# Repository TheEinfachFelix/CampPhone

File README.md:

# CampPhone

https://wolles-elektronikkiste.de/sim800l-modul

Gruppen Anruf
https://stackoverflow.com/questions/60790790/how-can-i-start-a-conference-call-on-gsm-network

Datasheet
https://www.makershop.de/download/Datasheet_SIM800L.pdf

Infos zu sim800L
https://dasraspberrypi.de/sim800l-gsm-gps-raspberry-4/

Sim 1:  4915756785137

Warum habe ich mich dagegen entschieden, das Sim Modul selber zu implementieren? Ich habe kein Chip gefunden, der günstiger als das fertige Modul war, und ein Datenblatt in Englischer Sprache hat.

GPS Module:
https://www.lcsc.com/product-detail/GNSS-Modules_ZHONGKEWEI-ATGM336H-5N31_C90770.html

Doku Dazu
https://medium.com/@joshhrisko/portable-gps-tracker-with-arduino-3affead7ba12
Ne lib dazu
https://github.com/mikalhart/TinyGPSPlus

Zum Display
https://buyepaper.com/products/27-inch-e-ink-touch-screen-spi-interface-4-grayscale-gdey027t91-t01
https://de.aliexpress.com/item/1005004887416350.html?src=google&pdp_npi=4@dis!EUR!13.39!13.39!!!!!@!12000030898082751!ppc!!!

Daten
https://www.good-display.com/product/259.html

FT6336U Touch Chip

Hier ne lib fürs display
https://github.com/ZinggJM/GxEPD2

Und fürs Touch
https://github.com/aselectroworks/Arduino-FT6336U

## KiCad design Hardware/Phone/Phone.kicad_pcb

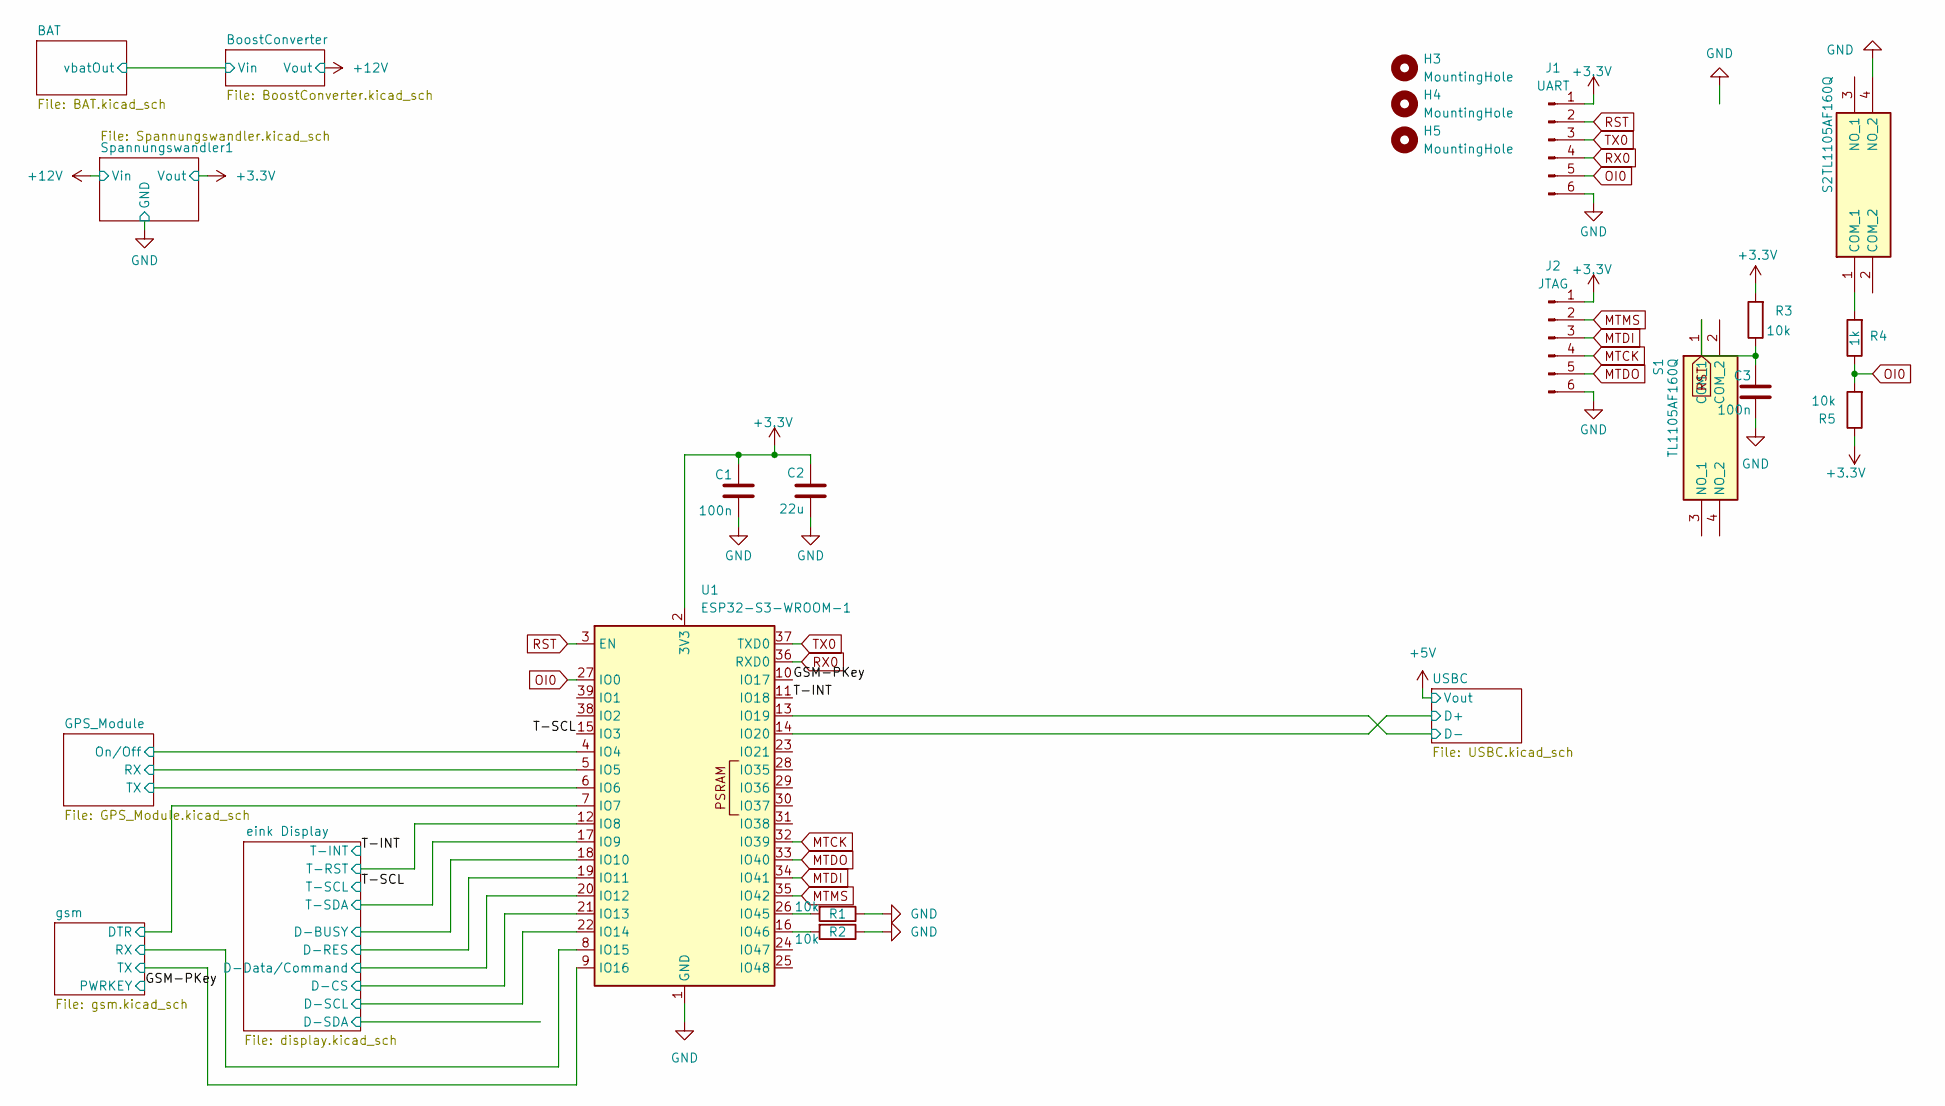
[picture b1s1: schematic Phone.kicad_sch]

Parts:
C1, C3: 100n; C_0603_1608Metric
C2: 22u; C_0603_1608Metric
H3, H4, H5: MountingHole; MountingHole_3.2mm_M3
J1: UART; 490107670612
J2: JTAG; 490107670612
R1, R2, R3, R5: 10k; R_0603_1608Metric
R4: 1k; R_0603_1608Metric
S1, S2: TL1105AF160Q; Mouser Part Number 612-TL1105A
U1: ESP32-S3-WROOM-1; ESP32-S3-WROOM-1U

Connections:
+3.3V: C1.2, C2.2, J1.1, J2.1, R3.2, R5.1, U1.2 (3V3); also elsewhere on the board
/GPS_Module/On/Off: U1.4 (IO4); also elsewhere on the board
/GPS_Module/RX: U1.5 (IO5); also elsewhere on the board
/GPS_Module/TX: U1.6 (IO6); also elsewhere on the board
/GSM-PKey: U1.10 (IO17); also elsewhere on the board
/T-INT: U1.11 (IO18); also elsewhere on the board
/T-SCL: U1.15 (IO3); also elsewhere on the board
/USBC/D+: U1.14 (IO20); also elsewhere on the board
/USBC/D-: U1.13 (IO19); also elsewhere on the board
/eink Display/D-BUSY: U1.18 (IO10); also elsewhere on the board
/eink Display/D-CS: U1.21 (IO13); also elsewhere on the board
/eink Display/D-Data/Command: U1.20 (IO12); also elsewhere on the board
/eink Display/D-RES: U1.19 (IO11); also elsewhere on the board
/eink Display/D-SCL: U1.22 (IO14); also elsewhere on the board
/eink Display/T-RST: U1.12 (IO8); also elsewhere on the board
/eink Display/T-SDA: U1.17 (IO9); also elsewhere on the board
/gsm/DTR: U1.7 (IO7); also elsewhere on the board
/gsm/RX: U1.8 (IO15); also elsewhere on the board
/gsm/TX: U1.9 (IO16); also elsewhere on the board
GND: C1.1, C2.1, C3.1, J1.6, J2.6, R1.1, R2.1, S2.4 (NO_2), U1.1 (GND), U1.40 (GND), U1.41 (GND); also elsewhere on the board
MTCK: J2.4, U1.32 (IO39)
MTDI: J2.3, U1.34 (IO41)
MTDO: J2.5, U1.33 (IO40)
MTMS: J2.2, U1.35 (IO42)
unnamed: R4.2, S2.1 (COM_1)
unnamed: R1.2, U1.26 (IO45)
unnamed: R2.2, U1.16 (IO46)
OI0: J1.5, R4.1, R5.2, U1.27 (IO0)
RST: C3.2, J1.2, R3.1, S1.1 (COM_1), U1.3 (EN)
RX0: J1.4, U1.36 (RXD0)
TX0: J1.3, U1.37 (TXD0)

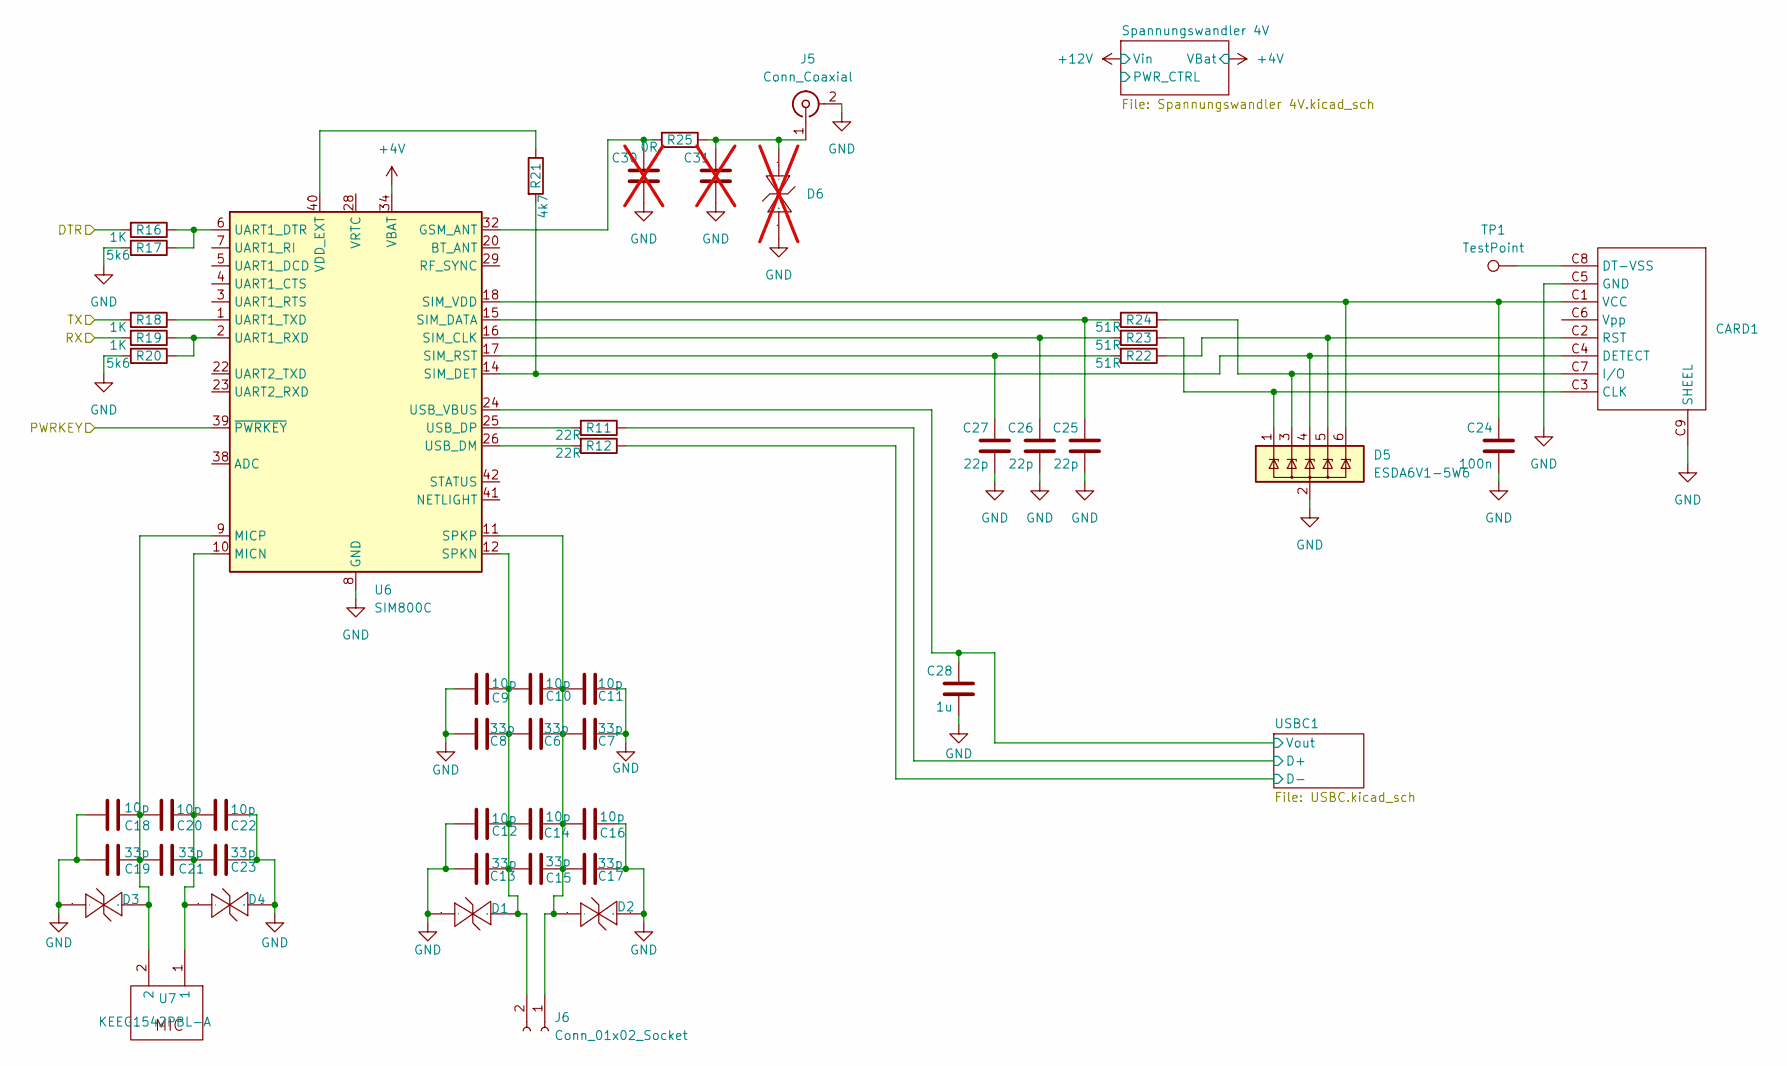
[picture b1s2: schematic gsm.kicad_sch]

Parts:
C6, C7, C8, C13, C15, C17, C19, C21, C23: 33p; C_0603_1608Metric
C9, C10, C11, C12, C14, C16, C18, C20, C22: 10p; C_0603_1608Metric
C24: 100n; C_0603_1608Metric
C25, C26, C27: 22p; C_0603_1608Metric
C28: 1u; C_0603_1608Metric
C30, C31: C_0603_1608Metric; not fitted
CARD1: SIM-SMD_503960-0696
D1, D2, D3, D4: SOD-882_L1.0-W0.6-BI
D5: ESDA6V1-5W6; SOT-363_SC-70-6
D6: SOD-882_L1.0-W0.6-BI; not fitted
J5: Conn_Coaxial; U.FL_Hirose_U.FL-R-SMT-1_Vertical
J6: Conn_01x02_Socket; PinHeader_1x02_P2.54mm_Vertical
R11, R12: 22R; R_0603_1608Metric
R16, R18, R19: 1K; R_0603_1608Metric
R17, R20: 5k6; R_0603_1608Metric
R21: 4k7; R_0603_1608Metric
R22, R23, R24: 51R; R_0603_1608Metric
R25: 0R; R_0603_1608Metric
TP1: TestPoint; TestPoint_Pad_D1.0mm
U6: SIM800C; SIMCom_SIM800C
U7: KEEG1542PBL-A; MIC-TH_BD4.0-P1.40_KEEG1542PBL-A

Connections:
+4V: U6.34 (VBAT), U6.35 (VBAT); also elsewhere on the board
/GSM-PKey: U6.39 (~PWRKEY); also elsewhere on the board
/gsm/DTR: R16.2; also elsewhere on the board
/gsm/RX: R19.2; also elsewhere on the board
/gsm/TX: R18.2; also elsewhere on the board
/gsm/USBC1/D+: R11.1; also elsewhere on the board
/gsm/USBC1/D-: R12.1; also elsewhere on the board
/gsm/USBC1/Vout: C28.2, U6.24 (USB_VBUS); also elsewhere on the board
GND: C7.1, C8.2, C9.2, C11.1, C12.2, C13.2, C16.1, C17.1, C18.2, C19.2, C22.1, C23.1, C24.1, C25.1, C26.1, C27.1, C28.1, C30.1, C31.1, CARD1.C5 (GND), CARD1.C9 (SHEEL), D1.1 (C), D2.2 (A), D3.1 (C), D4.2 (A), D5.2 (GND), D6.2 (A), J5.2 (Ext), R17.2, R20.2, U6.8 (GND), U6.13 (GND), U6.19 (GND), U6.21 (GND), U6.27 (GND), U6.30 (GND), U6.31 (GND), U6.33 (GND), U6.36 (GND), U6.37 (GND); also elsewhere on the board
unnamed: CARD1.C3 (CLK), D5.1 (IO1), R23.1
unnamed: CARD1.C4 (DETECT), D5.4 (IO3), R21.2, U6.14 (SIM_DET)
unnamed: CARD1.C8 (DT-VSS), TP1.1
unnamed: CARD1.C7 (I/O), D5.3 (IO2), R24.1
unnamed: CARD1.C2 (RST), D5.5 (IO4), R22.1
unnamed: C24.2, CARD1.C1 (VCC), D5.6 (IO5), U6.18 (SIM_VDD)
unnamed: C6.2, C8.1, C9.1, C10.2, C12.1, C13.1, C14.2, C15.2, D1.2 (A), J6.2, U6.12 (SPKN)
unnamed: C6.1, C7.2, C10.1, C11.2, C14.1, C15.1, C16.2, C17.2, D2.1 (C), J6.1, U6.11 (SPKP)
unnamed: C18.1, C19.1, C20.2, C21.2, D3.2 (A), U6.9 (MICP), U7.2
unnamed: C20.1, C21.1, C22.2, C23.2, D4.1 (C), U6.10 (MICN), U7.1
unnamed: C31.2, D6.1 (C), J5.1 (In), R25.1
unnamed: C30.2, R25.2, U6.32 (GSM_ANT)
unnamed: C26.2, R23.2, U6.16 (SIM_CLK)
unnamed: C25.2, R24.2, U6.15 (SIM_DATA)
unnamed: C27.2, R22.2, U6.17 (SIM_RST)
unnamed: R16.1, R17.1, U6.6 (UART1_DTR)
unnamed: R19.1, R20.1, U6.2 (UART1_RXD)
unnamed: R18.1, U6.1 (UART1_TXD)
unnamed: R12.2, U6.26 (USB_DM)
unnamed: R11.2, U6.25 (USB_DP)
unnamed: R21.1, U6.40 (VDD_EXT)

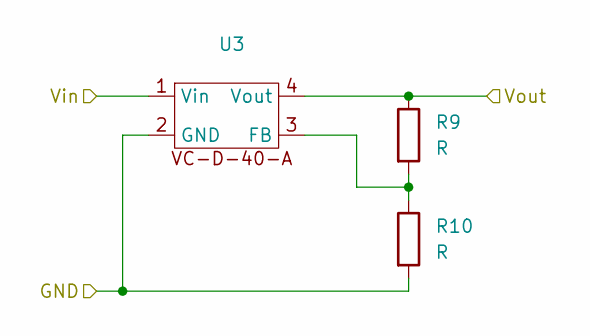
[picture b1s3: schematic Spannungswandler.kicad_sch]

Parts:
R9, R10: R; R_0805_2012Metric_Pad1.20x1.40mm_HandSolder
U3: VC-D-40-A

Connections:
+3.3V: R9.1, U3.4 (Vout); also elsewhere on the board
+12V: U3.1 (Vin); also elsewhere on the board
GND: R10.2, U3.2 (GND); also elsewhere on the board
unnamed: R9.2, R10.1, U3.3 (FB)

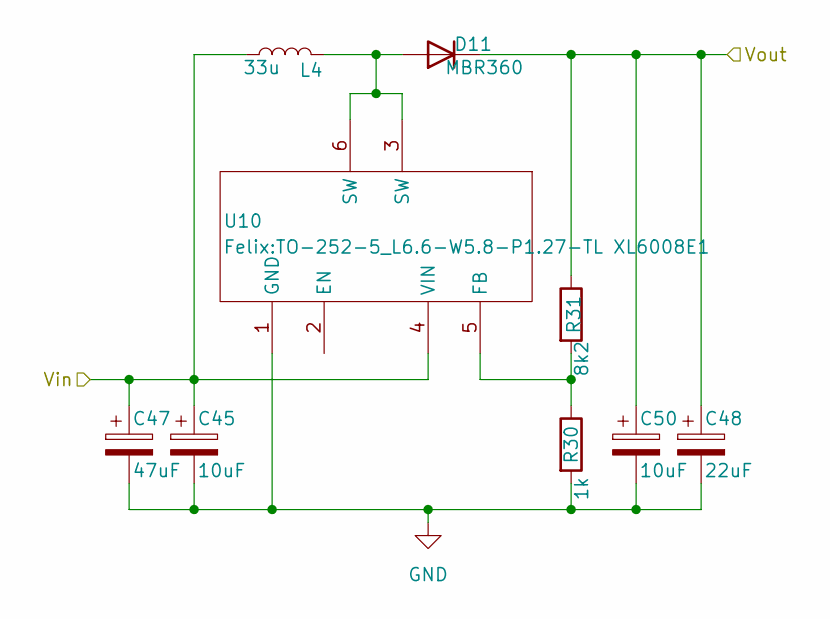
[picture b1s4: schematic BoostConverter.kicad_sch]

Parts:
C45, C50: 10uF; CP_Elec_4x5.4
C47: 47uF; CP_Elec_6.3x7.7
C48: 22uF; CP_Elec_10x10
D11: MBR360; TO-252-2
L4: 33u; L_7.3x7.3_H4.5
R30: 1k; R_0603_1608Metric
R31: 8k2; R_0603_1608Metric
U10: TO-252-5_L6.6-W5.8-P1.27-TL XL6008E1

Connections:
+12V: C48.1, C50.1, D11.1 (K), R31.1; also elsewhere on the board
/BAT/vbatOut: C45.1, C47.1, L4.1, U10.4 (VIN); also elsewhere on the board
GND: C45.2, C47.2, C48.2, C50.2, R30.2, U10.1 (GND); also elsewhere on the board
unnamed: D11.2 (A), L4.2, U10.3 (SW), U10.6 (SW)
unnamed: R30.1, R31.2, U10.5 (FB)

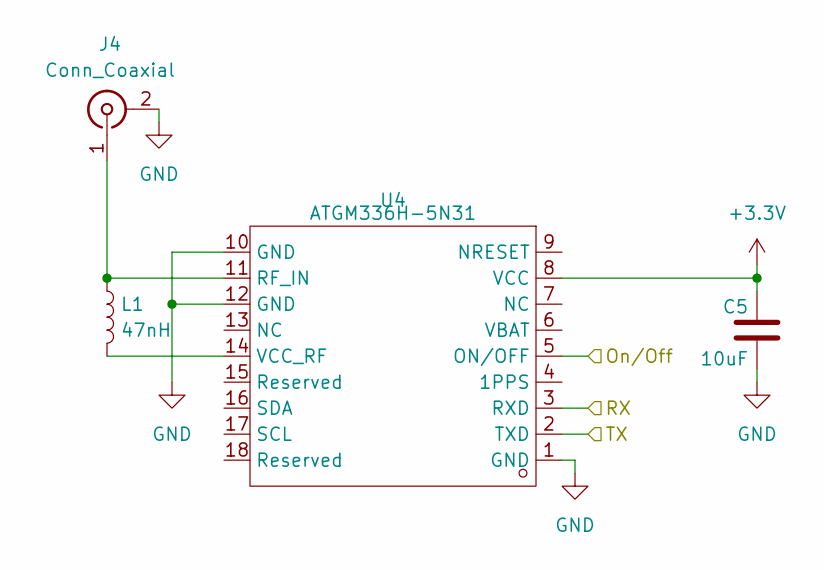
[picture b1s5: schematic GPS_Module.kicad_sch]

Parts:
C5: 10uF; C_0603_1608Metric
J4: Conn_Coaxial; U.FL_Hirose_U.FL-R-SMT-1_Vertical
L1: 47nH; L_0805_2012Metric
U4: ATGM336H-5N31; GPSM-SMD_ATGM336H-TR

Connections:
+3.3V: C5.2, U4.8 (VCC); also elsewhere on the board
/GPS_Module/On/Off: U4.5 (ON/OFF); also elsewhere on the board
/GPS_Module/RX: U4.3 (RXD); also elsewhere on the board
/GPS_Module/TX: U4.2 (TXD); also elsewhere on the board
GND: C5.1, J4.2 (Ext), U4.1 (GND), U4.10 (GND), U4.12 (GND); also elsewhere on the board
unnamed: J4.1 (In), L1.1, U4.11 (RF_IN)
unnamed: L1.2, U4.14 (VCC_RF)

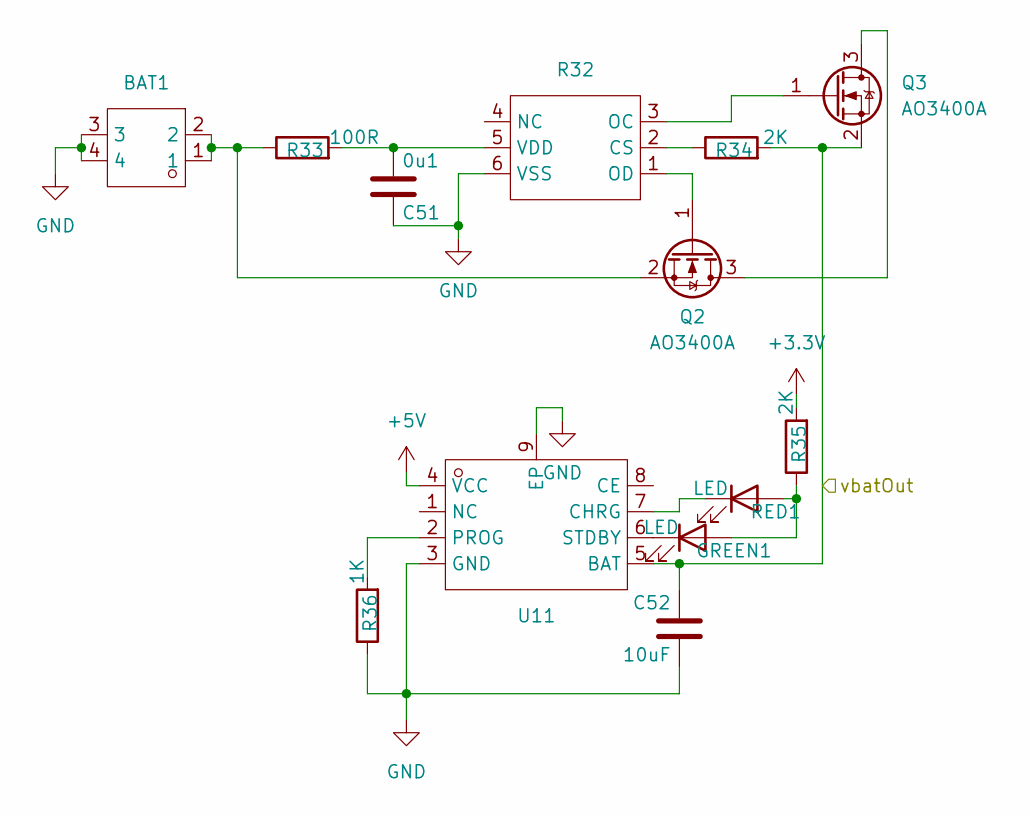
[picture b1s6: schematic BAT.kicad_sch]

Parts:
BAT1: BAT-TH_L77.0-W39.9_BH-18650-A1BJ021
C51: 0u1; C_0603_1608Metric
C52: 10uF; C_0603_1608Metric
GREEN1: LED; LED_0603_1608Metric
Q2, Q3: AO3400A; SOT-23
R32: SOT-23-6_L2.9-W1.6-P0.95-LS2.8-BR FM2113
R33: 100R; R_0603_1608Metric
R34, R35: 2K; R_0603_1608Metric
R36: 1K; R_0603_1608Metric
RED1: LED; LED_0603_1608Metric
U11: ESOP-8_L4.9-W3.9-P1.27-LS6.0-BL-EP

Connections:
+3.3V: R35.2; also elsewhere on the board
+5V: U11.4 (VCC); also elsewhere on the board
/BAT/vbatOut: C52.2, Q3.2 (S), R34.2, U11.5 (BAT); also elsewhere on the board
GND: BAT1.3, BAT1.4, C51.2, C52.1, R32.6 (VSS), R36.1, U11.3 (GND), U11.9 (EP); also elsewhere on the board
unnamed: GREEN1.2 (A), R35.1, RED1.2 (A)
unnamed: GREEN1.1 (K), U11.6 (STDBY)
unnamed: Q2.3 (D), Q3.3 (D)
unnamed: Q2.1 (G), R32.1 (OD)
unnamed: BAT1.1, BAT1.2, Q2.2 (S), R33.1
unnamed: Q3.1 (G), R32.3 (OC)
unnamed: R32.2 (CS), R34.1
unnamed: C51.1, R32.5 (VDD), R33.2
unnamed: RED1.1 (K), U11.7 (CHRG)
unnamed: R36.2, U11.2 (PROG)

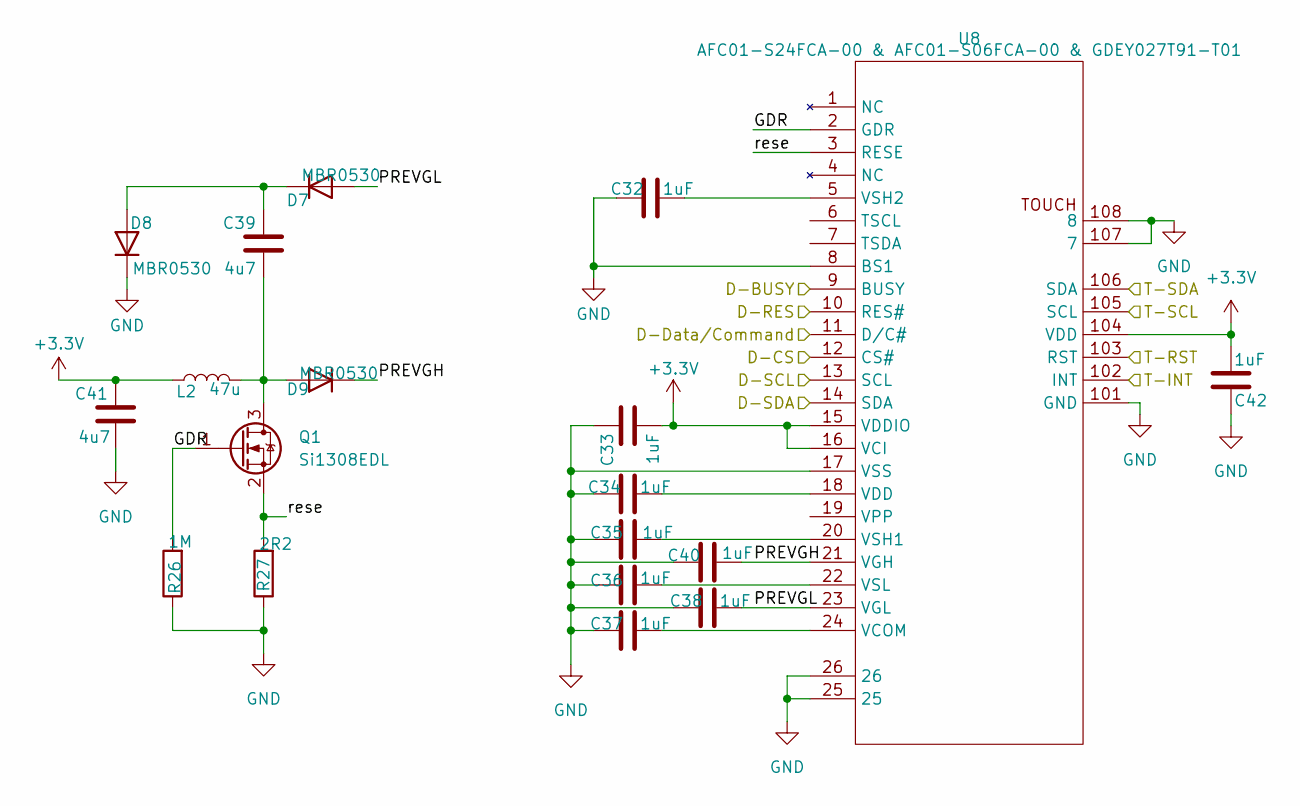
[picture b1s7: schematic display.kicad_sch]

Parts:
C32, C33, C34, C35, C36, C37, C38, C40, C42: 1uF; C_0603_1608Metric
C39, C41: 4u7; C_0603_1608Metric
D7, D8, D9: MBR0530; D_SOD-123
L2: 47u; IND-SMD_L4.0-W4.0 MNR4012
Q1: Si1308EDL; SOT-323_SC-70
R26: 1M; R_0603_1608Metric
R27: 2R2; R_0603_1608Metric
U8: AFC01-S24FCA-00 & AFC01-S06FCA-00 & GDEY027T91-T01; GDEY027T91-T01 Eink Touch LONG

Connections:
+3.3V: C33.1, C41.2, C42.1, L2.1, U8.15 (VDDIO), U8.16 (VCI), U8.104 (VDD); also elsewhere on the board
/T-INT: U8.102 (INT); also elsewhere on the board
/T-SCL: U8.105 (SCL); also elsewhere on the board
/eink Display/D-BUSY: U8.9 (BUSY); also elsewhere on the board
/eink Display/D-CS: U8.12 (CS#); also elsewhere on the board
/eink Display/D-Data/Command: U8.11 (D/C#); also elsewhere on the board
/eink Display/D-RES: U8.10 (RES#); also elsewhere on the board
/eink Display/D-SCL: U8.13 (SCL); also elsewhere on the board
/eink Display/D-SDA: U8.14 (SDA)
/eink Display/GDR: Q1.1 (G), R26.2, U8.2 (GDR)
/eink Display/PREVGH: C40.1, D9.1 (K), U8.21 (VGH)
/eink Display/PREVGL: C38.1, D7.2 (A), U8.23 (VGL)
/eink Display/T-RST: U8.103 (RST); also elsewhere on the board
/eink Display/T-SDA: U8.106 (SDA); also elsewhere on the board
/eink Display/rese: Q1.2 (S), R27.2, U8.3 (RESE)
GND: C32.2, C33.2, C34.2, C35.2, C36.2, C37.2, C38.2, C40.2, C41.1, C42.2, D8.1 (K), R26.1, R27.1, U8.8 (BS1), U8.17 (VSS), U8.25, U8.26, U8.101 (GND), U8.107 (7), U8.108 (8); also elsewhere on the board
unnamed: C34.1, U8.18 (VDD)
unnamed: C39.2, D7.1 (K), D8.2 (A)
unnamed: C39.1, D9.2 (A), L2.2, Q1.3 (D)
unnamed: C37.1, U8.24 (VCOM)
unnamed: C35.1, U8.20 (VSH1)
unnamed: C32.1, U8.5 (VSH2)
unnamed: C36.1, U8.22 (VSL)

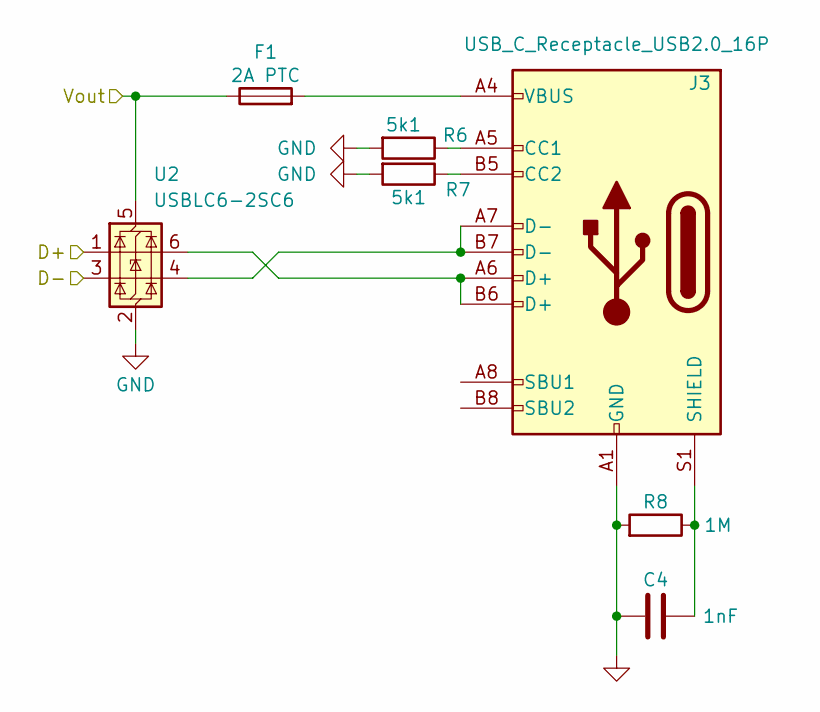
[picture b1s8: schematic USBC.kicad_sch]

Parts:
C4: 1nF; C_1206_3216Metric
F1: 2A PTC; Fuse_1206_3216Metric_Pad1.42x1.75mm_HandSolder
J3: USB_C_Receptacle_USB2.0_16P; USB_C_Receptacle_HRO_TYPE-C-31-M-12
R6, R7: 5k1; R_1206_3216Metric
R8: 1M; R_1206_3216Metric
U2: USBLC6-2SC6; SOT-23-6

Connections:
+5V: F1.1, U2.5 (VBUS); also elsewhere on the board
/USBC/D+: U2.1 (I/O1); also elsewhere on the board
/USBC/D-: U2.3 (I/O2); also elsewhere on the board
GND: C4.2, J3.A1 (GND), J3.A12 (GND), J3.B1 (GND), J3.B12 (GND), R6.2, R7.2, R8.2, U2.2 (GND); also elsewhere on the board
unnamed: F1.2, J3.A4 (VBUS), J3.A9 (VBUS), J3.B4 (VBUS), J3.B9 (VBUS)
unnamed: J3.A5 (CC1), R6.1
unnamed: J3.B5 (CC2), R7.1
unnamed: J3.A6 (D+), J3.B6 (D+), U2.6 (I/O1)
unnamed: J3.A7 (D-), J3.B7 (D-), U2.4 (I/O2)
unnamed: C4.1, J3.S1 (SHIELD), R8.1

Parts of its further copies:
C53: 1nF; C_1206_3216Metric
F3: 2A PTC; Fuse_1206_3216Metric_Pad1.42x1.75mm_HandSolder
J8: USB_C_Receptacle_USB2.0_16P; USB_C_Receptacle_HRO_TYPE-C-31-M-12
R37, R38: 5k1; R_1206_3216Metric
R39: 1M; R_1206_3216Metric
U12: USBLC6-2SC6; SOT-23-6

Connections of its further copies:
/gsm/USBC1/D+: U12.1 (I/O1); also elsewhere on the board
/gsm/USBC1/D-: U12.3 (I/O2); also elsewhere on the board
/gsm/USBC1/Vout: F3.1, U12.5 (VBUS); also elsewhere on the board
GND: C53.2, J8.A1 (GND), J8.A12 (GND), J8.B1 (GND), J8.B12 (GND), R37.2, R38.2, R39.2, U12.2 (GND); also elsewhere on the board
unnamed: F3.2, J8.A4 (VBUS), J8.A9 (VBUS), J8.B4 (VBUS), J8.B9 (VBUS)
unnamed: J8.A5 (CC1), R37.1
unnamed: J8.B5 (CC2), R38.1
unnamed: J8.A6 (D+), J8.B6 (D+), U12.6 (I/O1)
unnamed: J8.A7 (D-), J8.B7 (D-), U12.4 (I/O2)
unnamed: C53.1, J8.S1 (SHIELD), R39.1

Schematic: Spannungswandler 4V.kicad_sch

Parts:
C43: 330u; C_Elec_6.3x7.7
C44: 1u; C_0603_1608Metric
C46: 100n; C_0603_1608Metric
C49: 100u; C_Elec_8x10.2
D10: MBR360; TO-252-2
FB1: FerriteBead 270R @ 100Mhz; L_1206_3216Metric
L3: 100u; IND-SMD_L10.6-W10.2 2A 11x10mm
R28: 2k2; R_0603_1608Metric
R29: 1k; R_0603_1608Metric
U9: LM2596S-ADJ; TO-263-5_TabPin3

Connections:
+4V: FB1.1; also elsewhere on the board
+12V: C44.2, C49.1, U9.1 (VIN); also elsewhere on the board
/gsm/Spannungswandler 4V/PWR_CTRL: U9.5 (~ON/OFF)
GND: C43.2, C44.1, C46.1, C49.2, D10.2 (A), R29.2, U9.3 (GND); also elsewhere on the board
unnamed: C43.1, C46.2, FB1.2, L3.2, R28.1
unnamed: D10.1 (K), L3.1, U9.2 (OUT)
unnamed: R28.2, R29.1, U9.4 (FB)

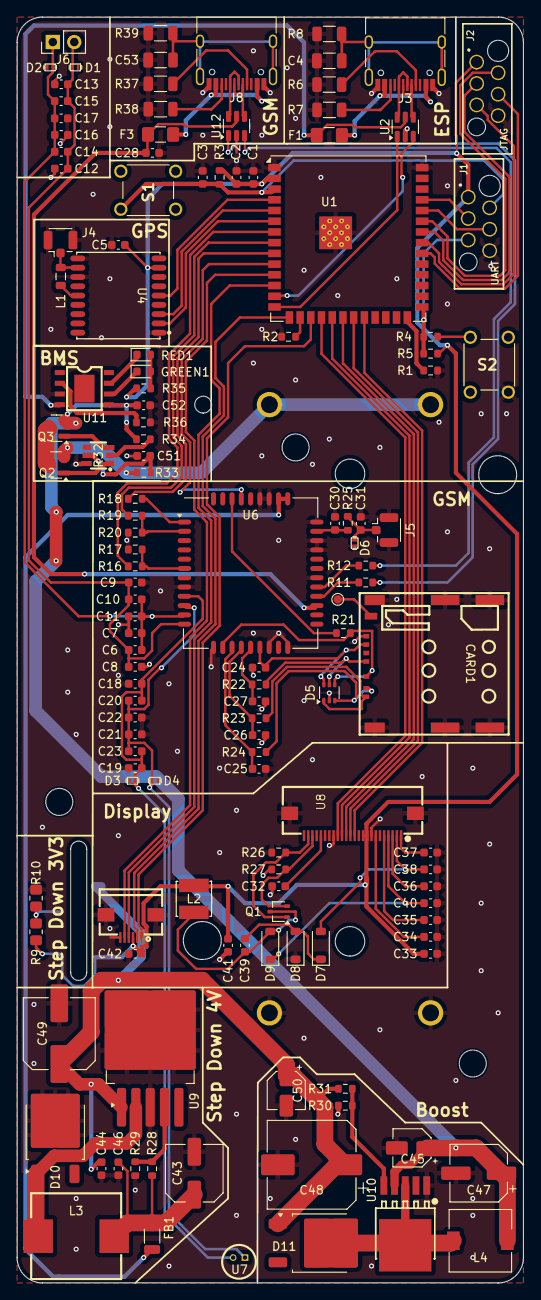
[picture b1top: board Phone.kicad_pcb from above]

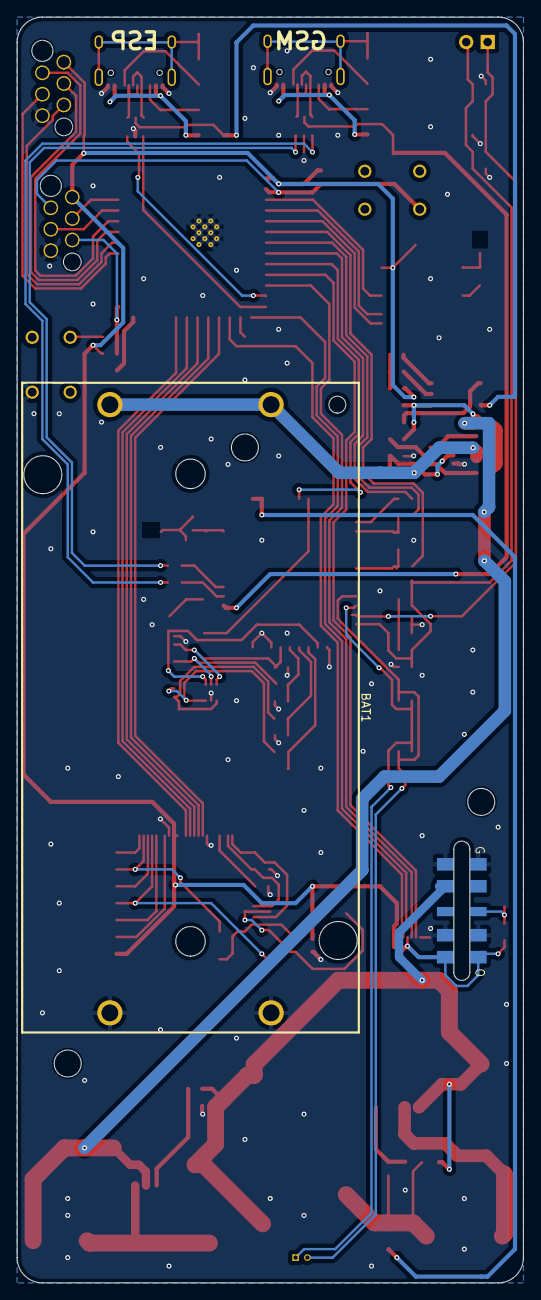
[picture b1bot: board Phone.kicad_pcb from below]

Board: 2 copper layers, 60.0 x 150.0 mm, 137 parts (2 on the bottom side), 100 nets.

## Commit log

2025-04-13 some Code
2025-04-15 working
2025-04-16 now with hardware serial
2025-04-16 jetzt mir Software serial
2025-04-16 kleine anpassungen
2025-04-17 demo is done
2025-04-22 started hardware design
2025-04-24 e ink is done
2025-04-27 phone design is done abendoning projekt
2025-04-27 added doku. Abendoning Projekt
2025-06-28 stuff
